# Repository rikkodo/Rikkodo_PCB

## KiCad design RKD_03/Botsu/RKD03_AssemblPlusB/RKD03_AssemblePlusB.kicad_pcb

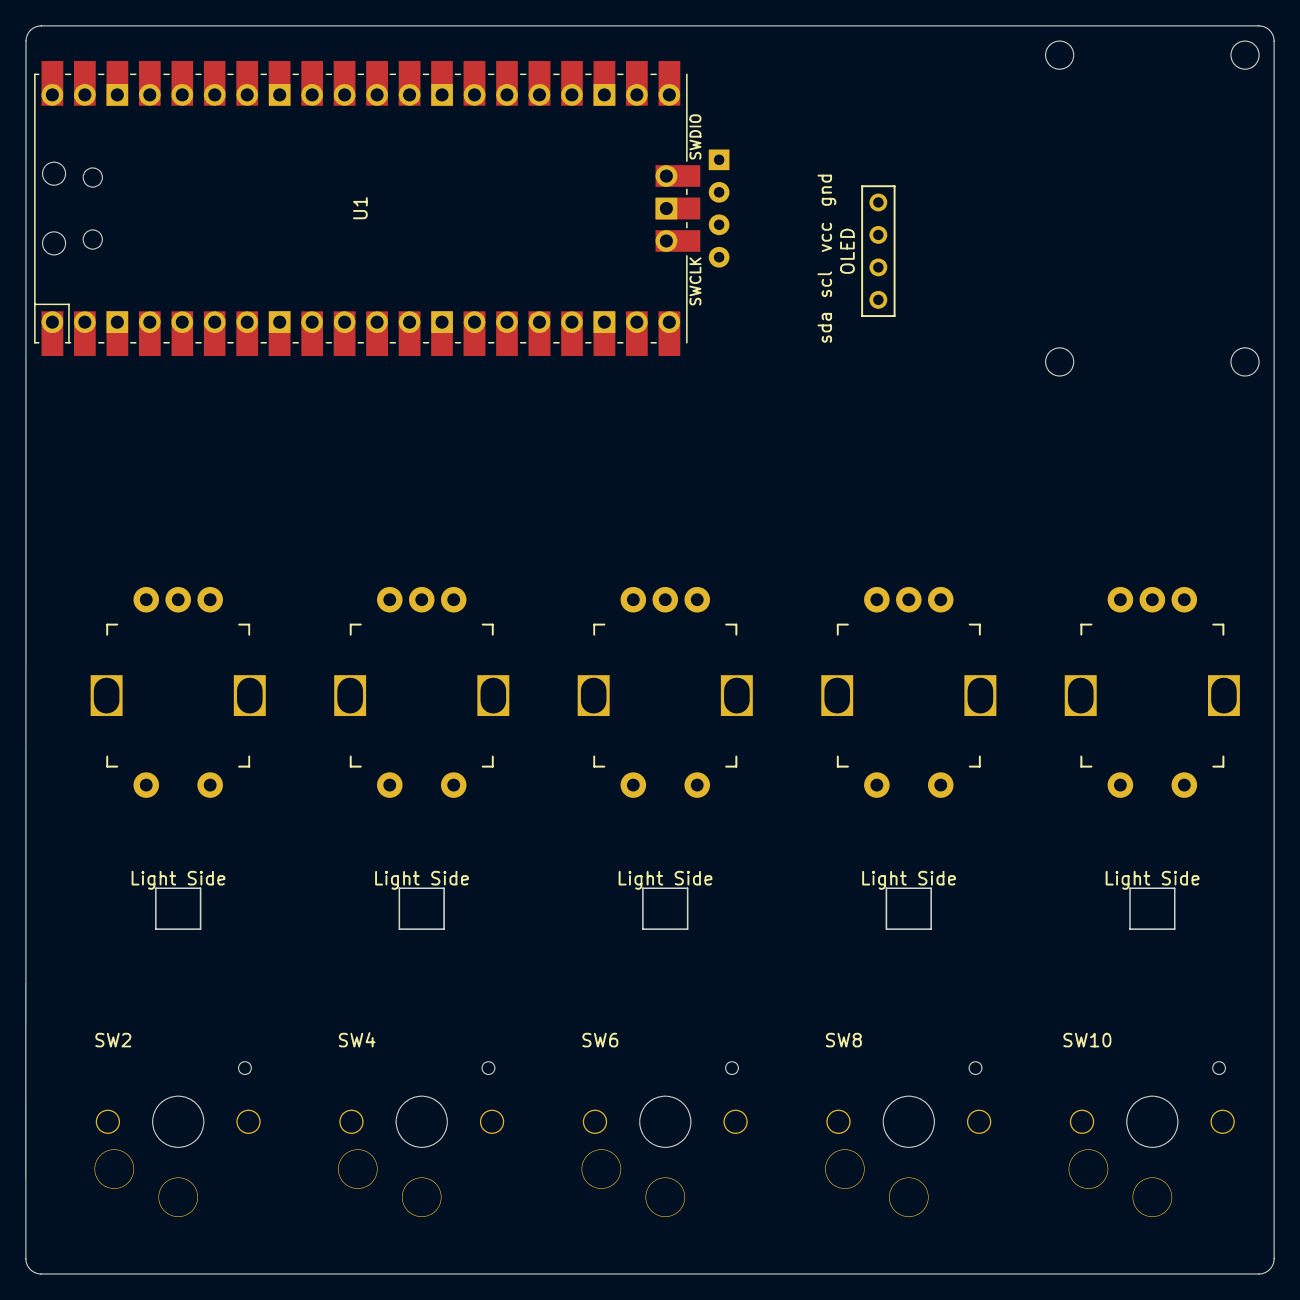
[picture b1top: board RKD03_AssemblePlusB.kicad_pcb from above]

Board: 2 copper layers, 97.6 x 97.6 mm, 29 parts (0 on the bottom side), 36 nets, no tracks yet.

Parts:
D1, D2, D3, D4, D5, D6, D7, D8, D9, D10: D; Diode_SMD
LED1, LED2, LED3, LED4, LED5: LED_SK6812MINI-E; LED_SK6812MINI-E_BL
OL1: OLED; OLED_center_display
OL2: OLED
Point1: PointScrewHall; rkd_Point_Screw_Hall
SW1, SW3, SW5, SW7, SW9: RotaryEncoder_Switch; RotaryEncoder_EC12E
SW2, SW4, SW6, SW8, SW10: SW_Push; Choc_Hotswap_1u
U1: Pico; RPi_Pico_SMD_TH

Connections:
Col0: SW1.S2, SW2.2, U1.5 (GPIO3)
Col1: SW3.S2, SW4.2, U1.11 (GPIO8)
Col2: SW5.S2, SW6.2, U1.16 (GPIO12)
Col3: SW7.S2, SW8.2, U1.20 (GPIO15)
Col4: SW9.S2, SW10.2, U1.21 (GPIO16)
GND: LED1.2 (VSS), LED2.2 (VSS), LED3.2 (VSS), LED4.2 (VSS), LED5.2 (VSS), OL1.4 (GND), OL2.4 (GND), SW1.C, SW3.C, SW5.C, SW7.C, SW9.C, U1.3 (GND), U1.8 (GND), U1.13 (GND), U1.18 (GND), U1.23 (GND), U1.28 (GND), U1.38 (GND)
LED: LED1.3 (DIN), U1.1 (GPIO0)
unnamed: D1.2 (A), SW1.S1
unnamed: D2.2 (A), SW2.1
unnamed: D3.2 (A), SW3.S1
unnamed: D4.2 (A), SW4.1
unnamed: D5.2 (A), SW5.S1
unnamed: D6.2 (A), SW6.1
unnamed: D7.2 (A), SW7.S1
unnamed: D8.2 (A), SW8.1
unnamed: D9.2 (A), SW9.S1
unnamed: D10.2 (A), SW10.1
unnamed: LED1.1 (DOUT), LED2.3 (DIN)
unnamed: LED2.1 (DOUT), LED3.3 (DIN)
unnamed: LED3.1 (DOUT), LED4.3 (DIN)
unnamed: LED4.1 (DOUT), LED5.3 (DIN)
RE1_A: SW1.A, U1.4 (GPIO2)
RE1_B: SW1.B, U1.2 (GPIO1)
RE2_A: SW3.A, U1.14 (GPIO10)
RE2_B: SW3.B, U1.12 (GPIO9)
RE3_A: SW5.A, U1.19 (GPIO14)
RE3_B: SW5.B, U1.17 (GPIO13)
RE4_A: SW7.A, U1.27 (GPIO21)
RE4_B: SW7.B, U1.29 (GPIO22)
RE5_A: SW9.A, U1.22 (GPIO17)
RE5_B: SW9.B, U1.24 (GPIO18)
Row0: D1.1 (K), D3.1 (K), D5.1 (K), D7.1 (K), D9.1 (K), U1.10 (GPIO7)
Row1: D2.1 (K), D4.1 (K), D6.1 (K), D8.1 (K), D10.1 (K), U1.9 (GPIO6)
SCL: OL1.2 (SCL), OL2.2 (SCL), U1.7 (GPIO5)
SDA: OL1.1 (SDA), OL2.1 (SDA), U1.6 (GPIO4)
VCC: LED1.4 (VDD), LED2.4 (VDD), LED3.4 (VDD), LED4.4 (VDD), LED5.4 (VDD), OL1.3 (VCC), OL2.3 (VCC), U1.40 (VBUS)

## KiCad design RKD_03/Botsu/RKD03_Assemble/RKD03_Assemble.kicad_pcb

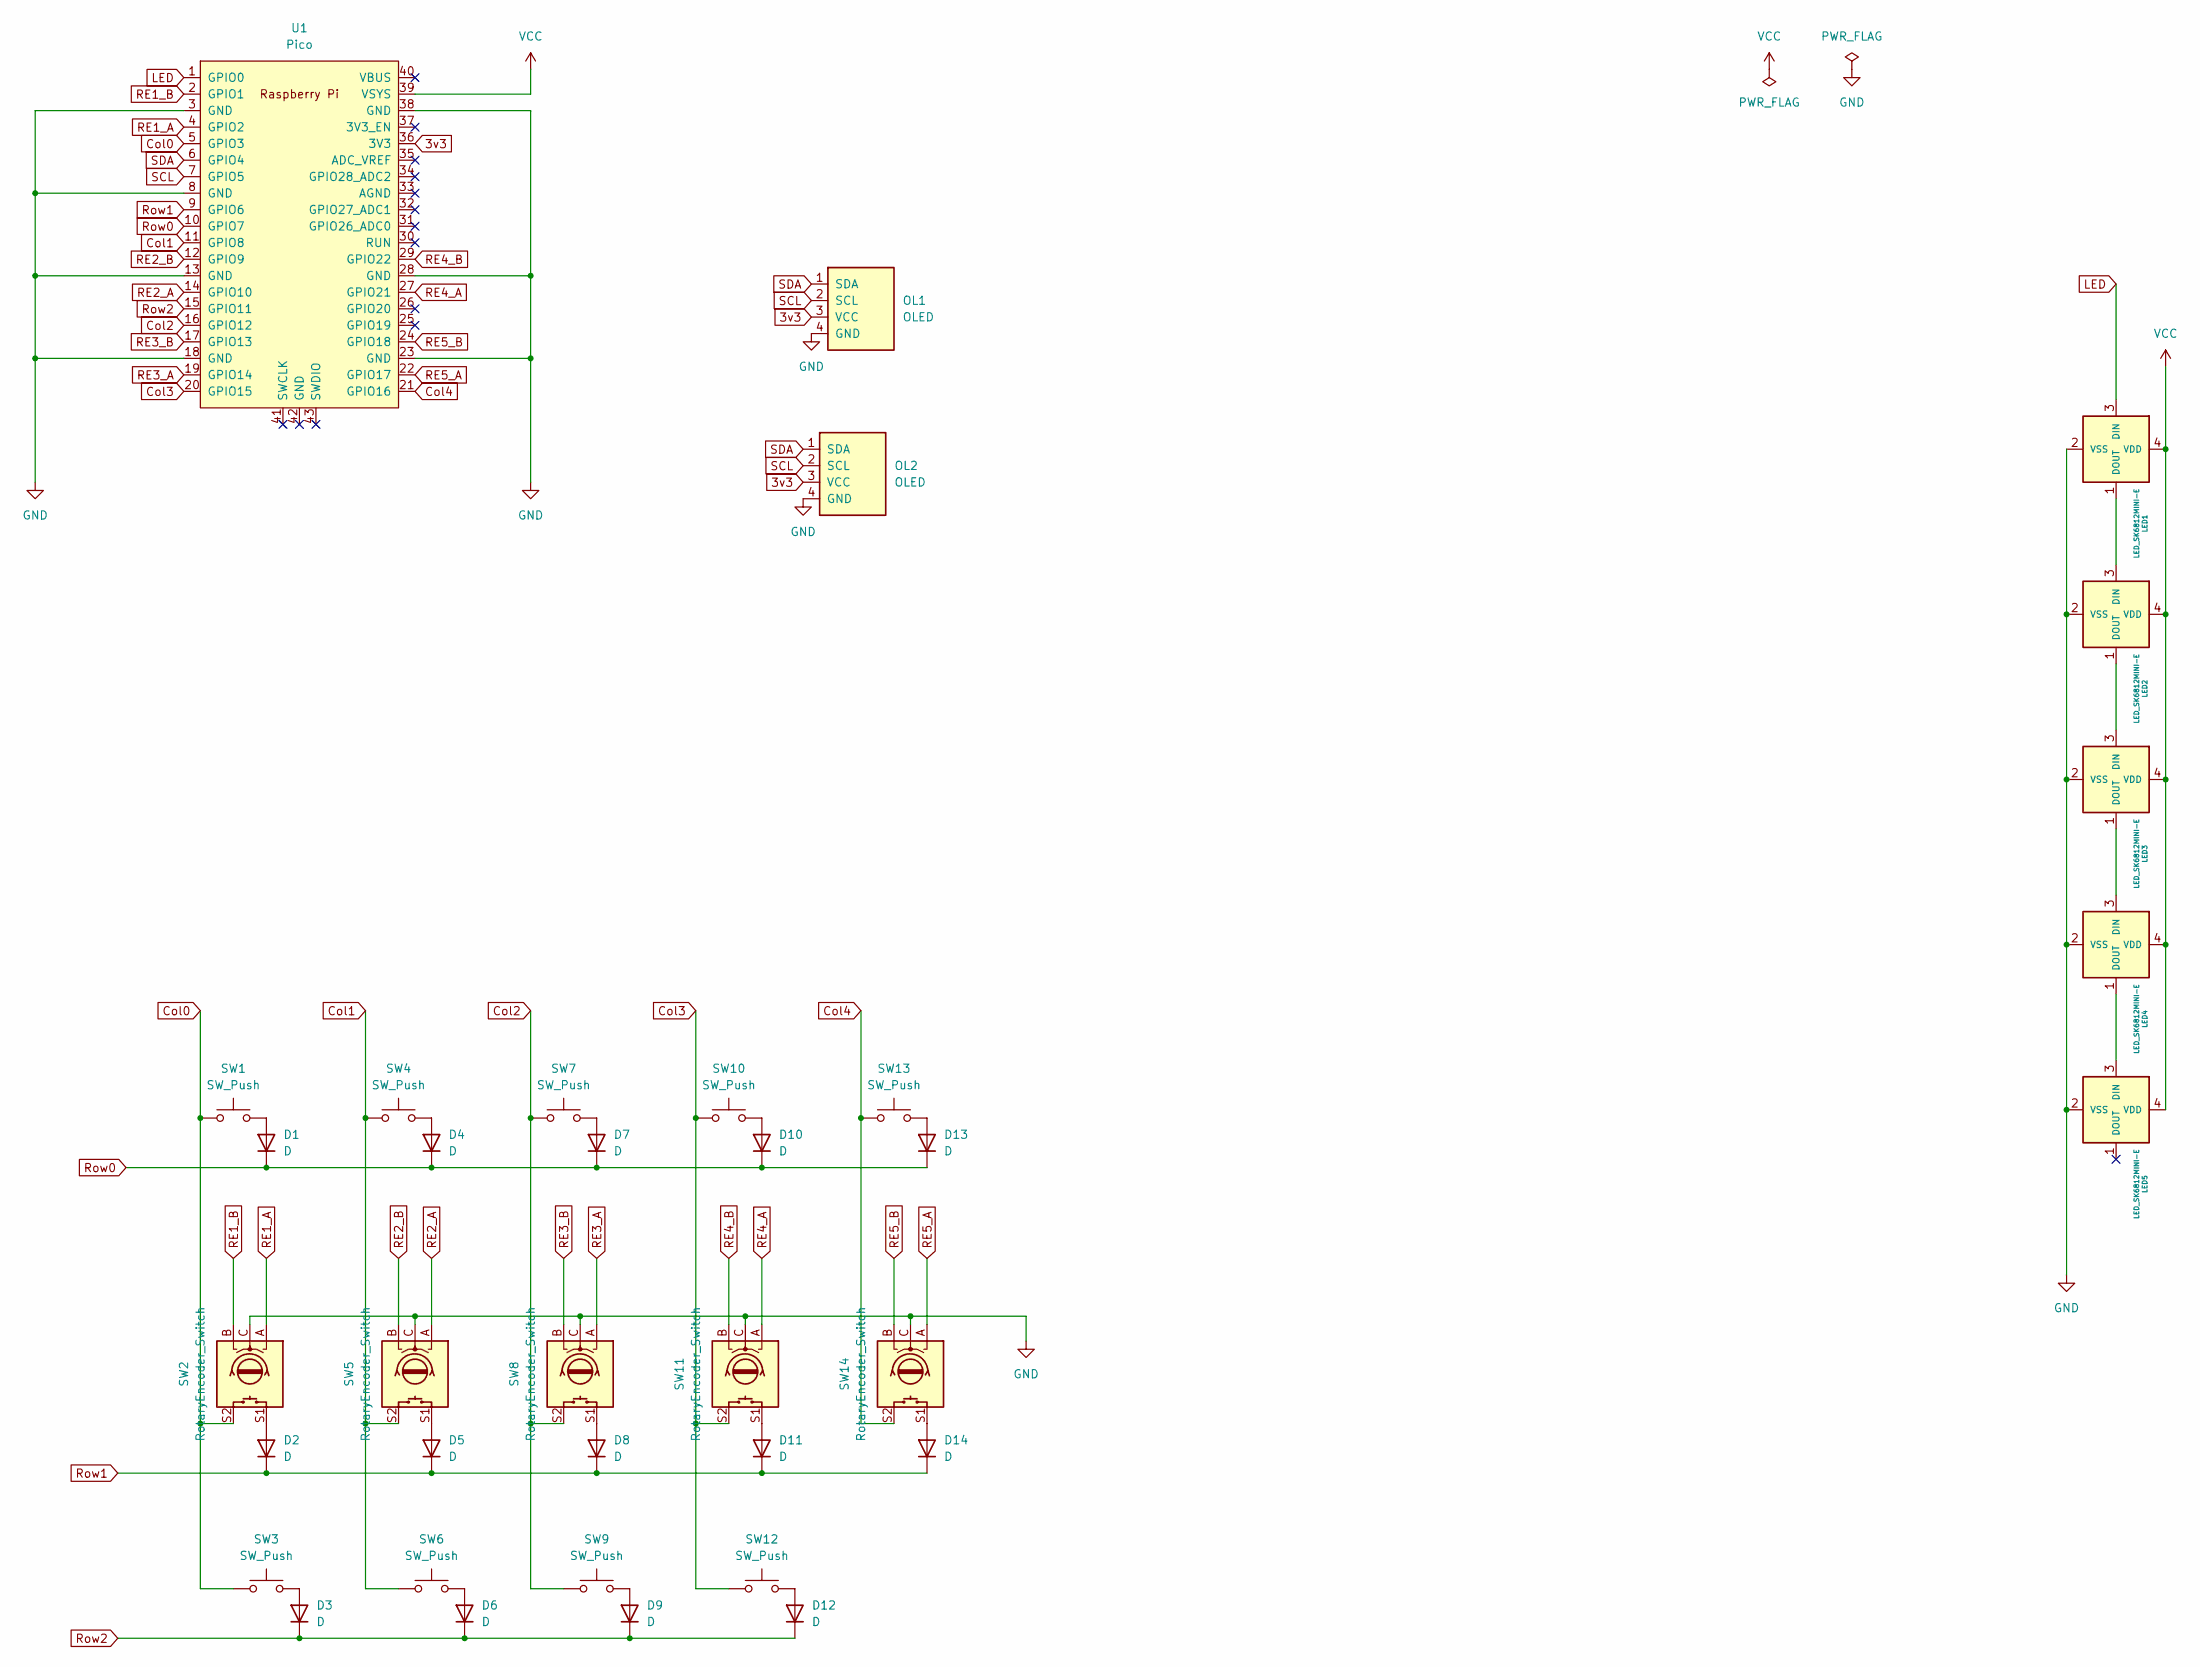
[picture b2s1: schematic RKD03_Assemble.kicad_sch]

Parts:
D1, D2, D3, D4, D5, D6, D7, D8, D9, D10, D11, D12, D13, D14: D; Diode_SMD
LED1, LED2, LED3, LED4, LED5: LED_SK6812MINI-E; LED_SK6812MINI-E_BL
OL1: OLED; OLED_center_display
OL2: OLED
SW1, SW3, SW4, SW6, SW7, SW9, SW10, SW13: SW_Push; rkd_Choc_v1v2_Hotswap_1u
SW2, SW5, SW8, SW11, SW14: RotaryEncoder_Switch; RotaryEncoder_EC12E
SW12: SW_Push; rkd_Choc_v1v2_Hotswap_2u_Gat
U1: Pico; rkd_RPi_Pico_TH

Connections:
3v3: OL1.3 (VCC), OL2.3 (VCC), U1.36 (3V3)
Col0: SW1.2, SW2.S2, SW3.2, U1.5 (GPIO3)
Col1: SW4.2, SW5.S2, SW6.2, U1.11 (GPIO8)
Col2: SW7.2, SW8.S2, SW9.2, U1.16 (GPIO12)
Col3: SW10.2, SW11.S2, SW12.2, U1.20 (GPIO15)
Col4: SW13.2, SW14.S2, U1.21 (GPIO16)
GND: LED1.2 (VSS), LED2.2 (VSS), LED3.2 (VSS), LED4.2 (VSS), LED5.2 (VSS), OL1.4 (GND), OL2.4 (GND), SW2.C, SW5.C, SW8.C, SW11.C, SW14.C, U1.3 (GND), U1.8 (GND), U1.13 (GND), U1.18 (GND), U1.23 (GND), U1.28 (GND), U1.38 (GND)
LED: LED1.3 (DIN), U1.1 (GPIO0)
unnamed: D1.2 (A), SW1.1
unnamed: D2.2 (A), SW2.S1
unnamed: D3.2 (A), SW3.1
unnamed: D4.2 (A), SW4.1
unnamed: D5.2 (A), SW5.S1
unnamed: D6.2 (A), SW6.1
unnamed: D7.2 (A), SW7.1
unnamed: D8.2 (A), SW8.S1
unnamed: D9.2 (A), SW9.1
unnamed: D10.2 (A), SW10.1
unnamed: D11.2 (A), SW11.S1
unnamed: D12.2 (A), SW12.1
unnamed: D13.2 (A), SW13.1
unnamed: D14.2 (A), SW14.S1
unnamed: LED1.1 (DOUT), LED2.3 (DIN)
unnamed: LED2.1 (DOUT), LED3.3 (DIN)
unnamed: LED3.1 (DOUT), LED4.3 (DIN)
unnamed: LED4.1 (DOUT), LED5.3 (DIN)
RE1_A: SW2.A, U1.4 (GPIO2)
RE1_B: SW2.B, U1.2 (GPIO1)
RE2_A: SW5.A, U1.14 (GPIO10)
RE2_B: SW5.B, U1.12 (GPIO9)
RE3_A: SW8.A, U1.19 (GPIO14)
RE3_B: SW8.B, U1.17 (GPIO13)
RE4_A: SW11.A, U1.27 (GPIO21)
RE4_B: SW11.B, U1.29 (GPIO22)
RE5_A: SW14.A, U1.22 (GPIO17)
RE5_B: SW14.B, U1.24 (GPIO18)
Row0: D1.1 (K), D4.1 (K), D7.1 (K), D10.1 (K), D13.1 (K), U1.10 (GPIO7)
Row1: D2.1 (K), D5.1 (K), D8.1 (K), D11.1 (K), D14.1 (K), U1.9 (GPIO6)
Row2: D3.1 (K), D6.1 (K), D9.1 (K), D12.1 (K), U1.15 (GPIO11)
SCL: OL1.2 (SCL), OL2.2 (SCL), U1.7 (GPIO5)
SDA: OL1.1 (SDA), OL2.1 (SDA), U1.6 (GPIO4)
VCC: LED1.4 (VDD), LED2.4 (VDD), LED3.4 (VDD), LED4.4 (VDD), LED5.4 (VDD), U1.39 (VSYS)

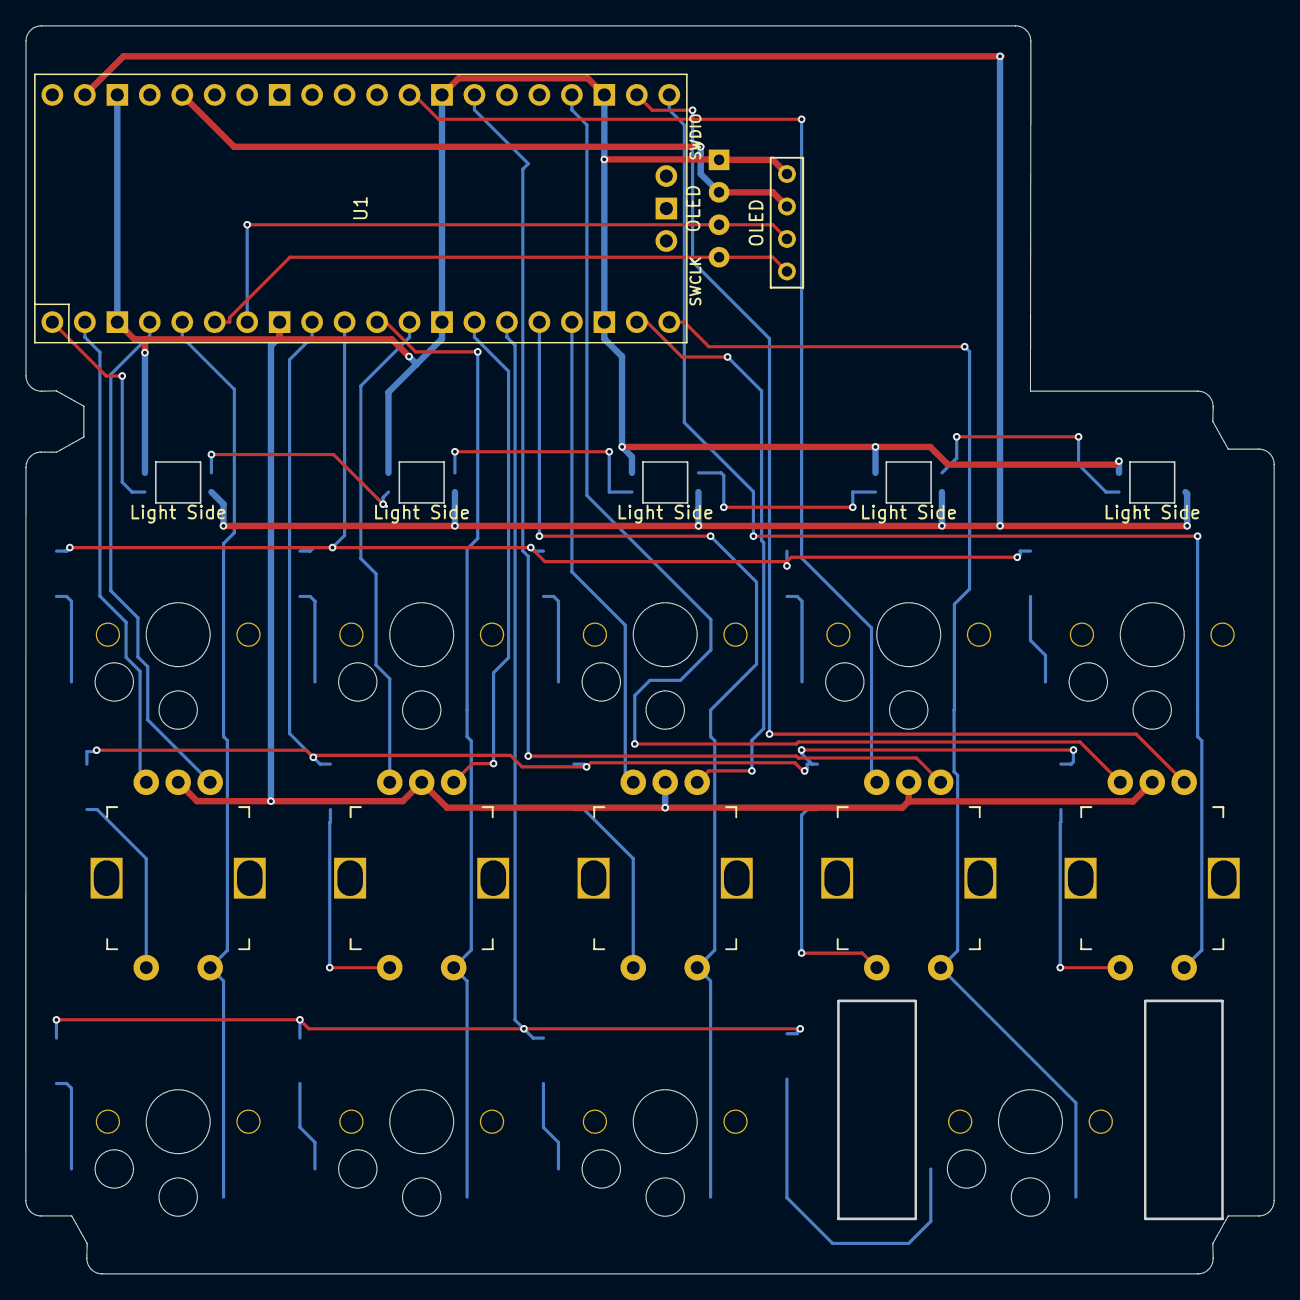
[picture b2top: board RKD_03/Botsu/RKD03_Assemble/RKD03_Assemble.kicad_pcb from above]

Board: 2 copper layers, 97.7 x 97.6 mm, 36 parts (0 on the bottom side), 42 nets.

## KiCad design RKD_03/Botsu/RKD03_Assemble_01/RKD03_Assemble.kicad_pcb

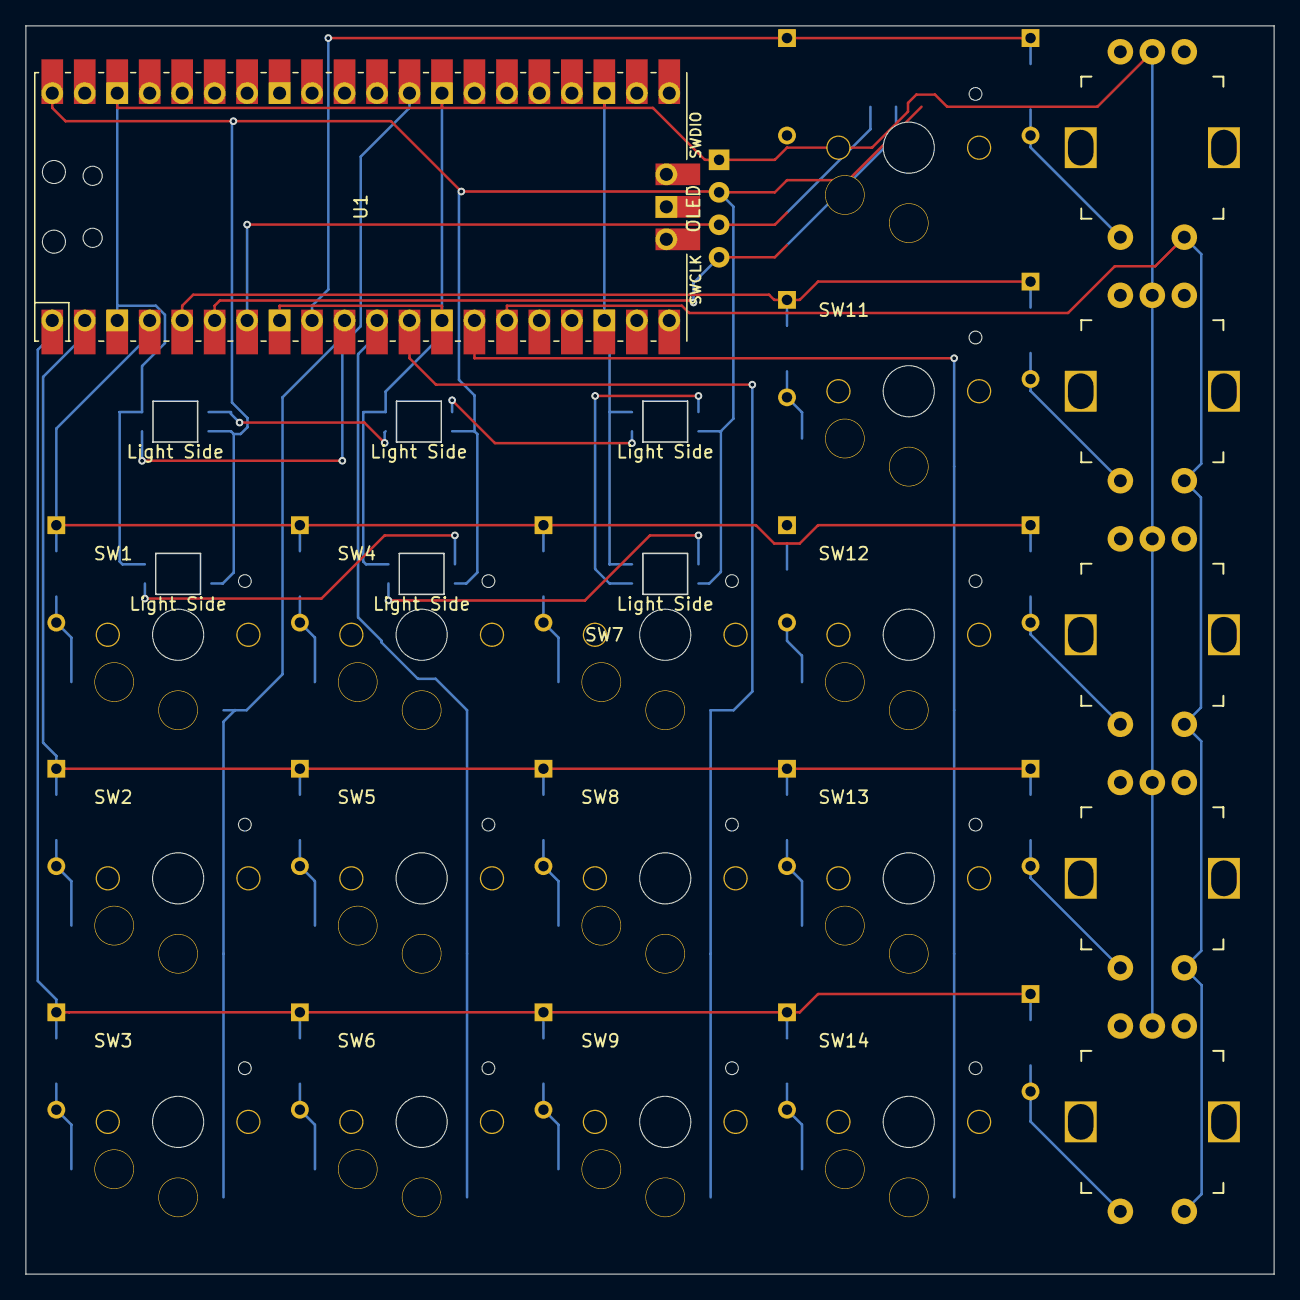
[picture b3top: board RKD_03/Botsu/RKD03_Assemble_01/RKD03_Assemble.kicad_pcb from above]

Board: 2 copper layers, 97.6 x 97.6 mm, 46 parts (0 on the bottom side), 39 nets.

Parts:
D1, D2, D3, D4, D5, D6, D7, D8, D9, D10, D11, D12, D13, D14, D15, D16, D17, D18, D19: D; Diode_TH_SMD
LED1, LED2, LED3, LED4, LED5, LED6: LED_SK6812MINI-E; LED_SK6812MINI-E_BL
OL1: OLED; OLED_center_display
SW1, SW2, SW3, SW4, SW5, SW6, SW7, SW8, SW9, SW10, SW11, SW12, SW13, SW14: SW_Push; Choc_Hotswap_1u
SW15, SW16, SW17, SW18, SW19: RotaryEncoder_Switch; RotaryEncoder_EC12E
U1: Pico; RPi_Pico_SMD_TH

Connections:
Col0: SW1.2, SW2.2, SW3.2, U1.10 (GPIO7)
Col1: SW4.2, SW5.2, SW6.2, U1.11 (GPIO8)
Col2: SW7.2, SW8.2, SW9.2, U1.12 (GPIO9)
Col3: SW11.2, SW12.2, SW13.2, SW14.2, U1.14 (GPIO10)
Col4: SW15.S2, SW16.S2, SW17.S2, SW18.S2, SW19.S2, U1.15 (GPIO11)
GND: LED1.2 (VSS), LED2.2 (VSS), LED3.2 (VSS), LED4.2 (VSS), LED5.2 (VSS), LED6.2 (VSS), OL1.4 (GND), SW15.C, SW16.C, SW17.C, SW18.C, SW19.C, U1.3 (GND), U1.8 (GND), U1.13 (GND), U1.18 (GND), U1.23 (GND), U1.28 (GND), U1.38 (GND)
LED: LED1.3 (DIN), U1.29 (GPIO22)
unnamed: D1.2 (A), SW1.1
unnamed: D2.2 (A), SW2.1
unnamed: D3.2 (A), SW3.1
unnamed: D4.2 (A), SW4.1
unnamed: D5.2 (A), SW5.1
unnamed: D6.2 (A), SW6.1
unnamed: D7.2 (A), SW7.1
unnamed: D8.2 (A), SW8.1
unnamed: D9.2 (A), SW9.1
unnamed: D10.2 (A), SW10.1
unnamed: D11.2 (A), SW11.1
unnamed: D12.2 (A), SW12.1
unnamed: D13.2 (A), SW13.1
unnamed: D14.2 (A), SW14.1
unnamed: D15.2 (A), SW15.S1
unnamed: D16.2 (A), SW16.S1
unnamed: D17.2 (A), SW17.S1
unnamed: D18.2 (A), SW18.S1
unnamed: D19.2 (A), SW19.S1
unnamed: LED1.1 (DOUT), LED2.3 (DIN)
unnamed: LED2.1 (DOUT), LED3.3 (DIN)
unnamed: LED3.1 (DOUT), LED4.3 (DIN)
unnamed: LED4.1 (DOUT), LED5.3 (DIN)
unnamed: LED5.1 (DOUT), LED6.3 (DIN)
Row0: D10.1 (K), D15.1 (K), U1.9 (GPIO6)
Row1: D11.1 (K), D16.1 (K), U1.5 (GPIO3)
Row2: D1.1 (K), D4.1 (K), D7.1 (K), D12.1 (K), D17.1 (K), U1.4 (GPIO2)
Row3: D2.1 (K), D5.1 (K), D8.1 (K), D13.1 (K), D18.1 (K), U1.2 (GPIO1)
Row4: D3.1 (K), D6.1 (K), D9.1 (K), D14.1 (K), D19.1 (K), U1.1 (GPIO0)
SCL: OL1.2 (SCL), U1.7 (GPIO5)
SDA: OL1.1 (SDA), U1.6 (GPIO4)
VCC: LED1.4 (VDD), LED2.4 (VDD), LED3.4 (VDD), LED4.4 (VDD), LED5.4 (VDD), LED6.4 (VDD), OL1.3 (VCC), U1.40 (VBUS)
